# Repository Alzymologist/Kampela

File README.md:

# Kampela
Hardware signer and key storage for Substrate ecosystem.
https://kampe.la

-------------------------------------------------
As of September 2023, this monorepo became really hard to work with, and had been splitted into multiple ones under the new [Kalapaja](https://github.com/Kalapaja) organisation.  
⚠️ This repo is kept up for archival reasons, please submit any issues and pull requests in that new org instead.

The new repository structure under Kalapaja is the following:

| New repository | Original subfolder | Description |
|----------------|--------------------|-------------|
|[kampela-firmware](https://github.com/Kalapaja/kampela-firmware)|[`firmware/development`](https://github.com/Alzymologist/Kampela/tree/main/firmware/development)|Firmware sources and associated software projects|
|[kampela-hardware](https://github.com/Kalapaja/kampela-hardware)|['hardware/development'](https://github.com/Alzymologist/Kampela/tree/main/hardware/development)|Hardware design schematics and supplementary files|
|[kampela-common](https://github.com/Kalapaja/kampela-common)|['common'](https://github.com/Alzymologist/Kampela/tree/main/common)|Collection of shared libraries used by both "hot" and "cold" side of the project|
|[siltti](https://github.com/Kalapaja/siltti)|[application](https://github.com/Alzymologist/Kampela/tree/main/application)|Android companion app to interface with the device|
|[docs](https://github.com/Kalapaja/docs)|[docs/development](https://github.com/Alzymologist/Kampela/tree/main/docs/development)|Miscellaneous docs documenting different aspects of the project|

-------------------------------------------------

## Project summary
Kampela is a hardware version of Parity Signer. It is a small card-shaped device (ideally comparable to a credit card form factor, to be carried in a wallet when needed) that accepts data through unidirectional NFC port and shows output on a monochrome electronic paper screen. It has cryptographic strongbox with elliptic curves supported by Substrate —  which only stores private keys (after initial import) and performs all signing operations on-chip.

Kampela is designed to be a comparatively low-cost (below €100, in contrast to €500+ for a Signer-compatible smartphone) single-purpose device, which would only support a single seed phrase per unit, operated via a drastically simplified user interface. However, it would have all the security features of Parity Signer: a full-featured SURI account derivation system, transactions preview, metadata updates, logging.

As something that supports the same QR code output formats as Signer, it would be able to drop-in replace Signer when providing signatures back to a mobile/desktop wallet. The only challenge would be in transforming the current QR-driven input format of Signer into a suitable NFC payload. Alongside with native support in some apps (which would require software modification) this can also be achieved with a tiny “translator” app for a regular (online, not necessary trusted — one’s usual daily driver) mobile phone: it would snap a QR code with the transaction details and (statelessly, without any extra features or complicated UI) transform that into an NFC payload.

Kampela is a natural (and long-discussed) extension of Parity Signer to leverage the most out of modern hardware-based crypto chips and drastically reduce Signer’s attack surface: no mobile OS, not extra platform features, no unexpected communication methods or airplane mode to take care of.

Kampela is not a wallet! It is a signing tool, it is not able to track on-chain balances, validate things over chain-provided information or generate transactions on itself.

## Problem statement

Parity Signer project is a unique solution to provide user-friendly secure airgapped signing with seamless integration into ecosystem. However, there are certain problems that could not be solved at the moment:

Hardware cryptographic chips in modern phones do not support elliptic curve algorithms used in Substrate networks — so in result secrets being exposed to the main RAM of the device for the duration of usage (only hardware-encrypted at rest), where it may potentially leak or be accessed by malicious software.

Current hardware compatibility is limited: only newer iOS devices and few latest models of Android devices support hardware encryption of secrets. This puts supported devices on the more expensive side of the price range.

With iPod Touch being decommissioned, all devices currently in production which support necessary hardware features also include baseband chip — which runs a separate closed-source OS running on a separate, special-purpose chip while commonly having a full DMA access to the main phone’s memory. This chip could not be trusted (see Samsung’s baseband backdoor as an example) and has potential to leak secrets through radio channel or by use of kleptography, overriding on-board entropy generation or execution environment.

## Details

Kampela is an approximately credit card sized box with a rectangular screen and minimalistic controls (capacitive buttons alongside the screen or something similar — to be designed). In addition to development of the device itself (which will be available under suitable FOSS licenses both in terms of software and hardware designs), a reference MVP implementation of QR-to-NFC converter app will also be created.

After seed phrase initialization (either input or random generation — the latter being a potential technical challenge due to its computational/UX intensity and lack of entropy available) it will be stored in an hardware-backed encrypted storage. Address derivations could be created in Kampela either by passing derivation strings from mobile device via NFC (since those are not secret on their own) or by typing on the device itself (with some form of dictionary-driven assisted input, due to limited controls available); resulting public keys could be exported through QR codes, in the exactly the same way as with Parity Signer. Transactions for signing are sent into Kampela via NFC, their contents rendered on low-power e-ink monochrome screen and then user can unlock the device and sign transaction. Unidirectional nature and limited range/direction of both communication interfaces ensures that user remains in full control of data. Kampela has no battery (at least no battery for long-term power supply) and is powered only through NFC — which adds another layer of security, since no long-term backdoors can survive in RAM, and compromising the stored firmware itself is a much higher bar to clear for the attackers. Kampela will use a Secure Element or similar technology (like Arm TrustZone) to store secrets in a way, which will make it as hard as realistically possible to extract the secret keys, even with full physical access to the device and lab equipment being available.

Kampela is envisioned to be as close to open hardware criteria as possible, as long as it won’t compromise the resulting security model directly (for example, if requirement to support arbitrary user-provided firmware would clash with chosen security model, we would choose security model; all such cases would be clearly argumented and documented, of course). All security-sensitive parts of the device (NFC, RNG) would be implemented as much as possible through discrete, fixed-logic components (potentially with FPGA for the more uncommon parts of it, like sr25519  crypto) instead of being done “in software” or trusted to all-in-one integrated chip developers. Firmware for the programmable part of the device is to be written in Rust. On the smartphone companion app, it would use the same proven combination of Rust and native platform-dependent frameworks as Parity Signer currently does.

Unlike other projects in the similar problem space (which routinely withheld certain design specifications, and make others only available under an NDA, see, for example, discontinued project Cobo), we aim to make an extreme push to transparency of our designs, both on hardware and software layers. While this is expected to provide a boost in security and verifiability of Kampela devices, this severely restricts any potential future commercialization effort, since the competition (which wouldn't have to recover R&D costs) would undercut any official manufacturers on profit margins. We'd prefer this extreme competition to be a feature, not a bug; the only project with comparable manufacturing model would be Trezor, but it has a series of well-known shortcomings both in design and hardware choice areas.

## Ecosystem Fit

Currently, there are not too many options to securely handle keys in the Polkadot/Kusama ecosystem. There’s some Ledger support (which is often lagging behind the runtimes update cadence, and doesn’t exist for all the parachains out of the box), and Parity Signer and it’s fork Stylo (which requires an expensive smartphone device being used for this airgapped purpose only, and also has a much wider attack surface due to the device having a general-purpose OS and at least potential WiFi/3G/Bluetooth connectivity). We expect Kampela (having its own set of quite distinct tradeoffs) to supplement those two solutions — and integrate nicely with other layers of the tech stack (wallets, browser extensions etc), being a drop-in replacement of the currently already broadely supported Parity Signer.

## Origins of the name

Kampela, a flatfish — since the device is flat and is intended to resist phishing.

## Why Polkadot network?

Kampela project is a long-missing component to ultimately harden security of the whole Substrate ecosystem and ensure it’s secure and unstoppable status in long-term. Polkadot part of the greater ecosystem, as flagship and stable reference core, is natural space to develop universal solid solution like Kampela.

## Reviewers responses

Q: ​I think the NFC part isn’t very great from a usability perspective.

A: On contrary, NFC transfer of data into the device would be much smoother than with QR movies, especially for large payloads like metadata. The idea is that user will attach Kampela to the back of the smartphone, perform all the operations that do not require security with convenience of familiar smartphone interfaces, then flip the stack over and perform secure operations until output QR is shown. With QR presented on e-ink screen, Kampela could safely be detached from the phone as the QR intended for public broadcast would remain on screen. The task of mechanical engineer in this project (in addition to making device casing cheap to produce and robust) would be to ensure this flow is as comfortable and universal across the phones as possible.

Q: I guess the user does not really care about the RAM exposure as long as my phone is offline all the time.

A: Unfortunately, this is not so. The applications that could corrupt memory used by the signing application could manipulate RNG into leaking arbitrary data (including leaked secrets) through kleptography methods without exposing the leakage in any way. The leaked secrets could be broadcasted secretly through signature screen or other non-disabled communication methods via steganography. Finally, secrets leaked to memory could be stored outside of hardware encrypted storage negating its benefits in case attacker has physical access to the device reducing his need for fully-equipped forensic lab to relatively cheap and widespread memory dumping equipment. The Kampela solves these issues by lack of shared execution environment (and potentially rogue independent blackbox systems on board) and solid rust code with proper zeroization implemented.

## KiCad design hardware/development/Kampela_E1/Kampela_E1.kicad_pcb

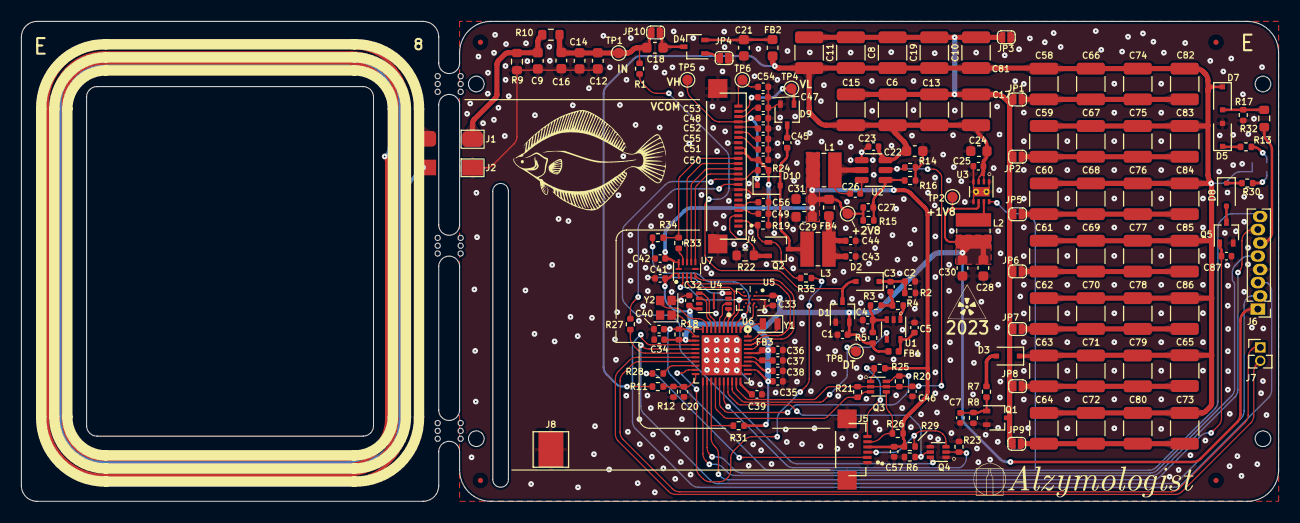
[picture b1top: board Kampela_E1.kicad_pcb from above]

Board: 2 copper layers, 120.5 x 46.0 mm, 188 parts (1 on the bottom side), 95 nets.

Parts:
C1, C4, C5, C20, C23, C25, C26, C32, C33, C35, C36, C37, C38, C40, C41, C42, C46: 0.1u; C_0402_1005Metric
C2: 82p; C_0402_1005Metric
C3, C27: 100p; C_0402_1005Metric
C6, C8, C10, C11, C13, C15, C17, C19, C58, C59, C60, C61, C62, C63, C64, C65, C66, C67, C68, C69, C70, C71, C72, C73, C74, C75, C76, C77, C78, C79, C80, C81, C82, C83, C84, C85, C86: 47x16; C_1210_3225Metric
C7: 1uF; C_0402_1005Metric
C9: NC; C_0603_1608Metric
C12, C14: 47; C_0603_1608Metric
C16: 100; C_0603_1608Metric
C18: 68; C_0603_1608Metric
C21, C22, C24: 10x16; C_0603_1608Metric
C28, C29, C30, C31: 22x6.3; C_0603_1608Metric
C34, C43, C45, C49, C52, C53, C56, C57, C87: 4.7x25; C_0402_1005Metric
C39, C47, C48, C50, C51, C54, C55: 1x50; C_0402_1005Metric
C44: 0.1; C_0402_1005Metric
D1: BAV99W; SOT-323_SC-70
D2, D7, D10: BAT54WS; D_SOD-323F
D3: BZX84J-B9V1; D_SOD-323F
D4, D9: BAS70-04W; SOT-323_SC-70
D5: D3Z13BF-7; D_SOD-323F
D8: D3Z5V1BF-7; D_SOD-323F
D12: SB0603WC01-RG; LED_DUAL_0603
FB1, FB3: BLM15AG102SZ1D; L_0402_1005Metric
FB2, FB4: BLM18KG102SN1D; L_0603_1608Metric
FID1, FID2, FID3, FID4: Fiducial; Fiducial_0.5mm_Mask1.5mm
H1, H2, H3, H4: MountingHole; MountingHole_2.1mm
J1, J2, J8: E_ANT; TestPoint_Pad_2.4x3.5mm
J4: E2154CS0C1; GDEY027T91-T01_bended
J5: TOUCH; HRS_FH34SRJ-6S-0.5SH(50)
J6: Conn_01x08; PinHeader_1x08_P1.27mm_Vertical_Prog
J7: Conn_01x02; PinHeader_1x02_P1.27mm_Vertical
JP1, JP2, JP3, JP4, JP5, JP6, JP7, JP8, JP9, JP10: SolderJumper_2_Open; SolderJumper_0.8.x1mm
L1: 3.3uH; L_Wuerth_MAPI-3015
L2: 2.2uH; L_Wuerth_MAPI-3015
L3: NR3015T100M; L_Wuerth_MAPI-3015
Q1, Q2: PMF250XNEX; SOT-323_SC-70
Q3, Q4: SSM6N35AFE; SOT-563
Q5: NX138BKWX; SOT-323_SC-70
R1: 6.8K; R_0402_1005Metric
R2: 53.6K; R_0402_1005Metric
R3: 22K; R_0402_1005Metric
R4: 47K; R_0402_1005Metric
R5: 100K; R_0402_1005Metric
R6, R7, R17, R18, R23, R24, R25, R26, R27, R28, R29: 10K; R_0402_1005Metric
R8, R11: 976K; R_0402_1005Metric
R9: 1K; R_0603_1608Metric
R10, R32: 2.2; R_0603_1608Metric
R12, R14: 150K; R_0402_1005Metric
R13: 10; R_0402_1005Metric
R15: 130K; R_0402_1005Metric
R16: 52.3K; R_0402_1005Metric
R19, R31: 470K; R_0402_1005Metric
R20, R21, R34, R35: 1K; R_0402_1005Metric
R22: 0.47R; R_0603_1608Metric
R30, R33: 100; R_0402_1005Metric
TP1, TP2, TP3, TP4, TP5, TP6, TP8: TestPoint; TestPoint_Pad_D1.0mm
U1: LMV7271; SOT-353_SC-70-5
U2: AP63200WU; TSOT-23-6
U3: TPS62171DSG; WSON-8-1EP_2x2mm_P0.5mm_EP0.9x1.6mm_ThermalVias
U4: APS6404L-SQN; SON-8-1EP_3x2mm_P0.5mm_EP1.4x1.6mm
U5: AT25XE321D-UUN-T; WLCSP 12-ball 3 x 2 x 3 Array
U6: EFM32PG23B200F512IM40; QFN-40_EP_5x5_Pitch0.4mm
U7: TXU0104PW; Texas_R-PUQFN-N12
Y1: FC2012AN; Crystal_SMD_2012-2Pin_2.0x1.2mm
Y2: 39MHz; Crystal_SMD_2016-4Pin_2.0x1.6mm
mouse-bite-2mm-slot, mouse-bite-2mm-slot#2, mouse-bite-2mm-slot#3: VAL**; mouse-bite-2mm_DEEP

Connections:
+1V8: C1.2, C28.2, C30.2, C32.1, C33.1, C34.2, C35.1, C36.1, C38.1, C41.2, D1.2 (K), FB1.1, FB3.2, J6.1, L2.2, R5.1, R18.2, R31.1, TP2.1, U3.6 (VOS), U4.8 (VCC), U5.B2 (VCC), U6.12 (DVDD), U6.32 (VREGVDD), U6.34 (DVDD), U6.36 (IOVDD), U7.1 (VCCA)
+2V8: C27.1, C29.2, C31.2, C42.1, C50.2, C57.1, FB4.2, J4.15, J4.16, J5.4, L1.2, R15.1, R24.2, R25.1, R26.1, R29.2, TP3.1, U7.11 (VCCB), U7.12 (OE)
/Display/2V8_EN: C46.1, Q3.2 (G), Q3.5 (G), R14.2, R20.2, R21.2, U2.2 (EN), U6.29 (PA09)
/Display/BUSY: R27.2, U6.15 (PB04)
/Display/E_BUSY: J4.9, R27.1
/Display/E_CS: U6.38 (PD02), U7.4 (A3)
/Display/E_D/C: U6.37 (PD03), U7.5 (A4)
/Display/E_MISO: R34.1, U5.D4 (IO1/SO), U6.2 (PC01)
/Display/E_RES: J4.10, Q4.6 (D), R24.1
/Display/E_SCK: U5.F2 (SCK), U6.4 (PC03), U7.3 (A2)
/Display/E_SDI: U5.E3 (SI/IO0), U6.3 (PC02), U7.2 (A1)
/Display/GDR: J4.2, Q2.1 (G), R19.1, R35.1
/Display/H_CS: J4.12, U7.8 (B3)
/Display/H_D/C: J4.11, U7.7 (B4)
/Display/H_SCK: J4.13, U7.9 (B2)
/Display/H_SDI: J4.14, R33.1, R34.2
/Display/INT: R28.2, U6.18 (PB01)
/Display/POW: C43.2, C44.1, FB4.1, L3.1
/Display/PREVGH: C48.1, D10.1 (K), J4.21, TP5.1
/Display/PREVGL: C47.1, D9.1, J4.23, TP4.1
/Display/RES: Q4.2 (G), R23.2, U6.26 (PA06)
/Display/RESE: J4.3, Q2.2 (S), R22.1
/Display/RES_TC: Q4.5 (G), R6.2, U6.27 (PA07)
/Display/SCL: Q3.3 (D), R21.1, U6.24 (PA04)
/Display/SDA: Q3.6 (D), R20.1, U6.25 (PA05)
/Display/T_INT: J5.2, R28.1
/Display/T_RES: J5.3, Q4.3 (D), R29.1
/Display/T_SCL: J5.5, Q3.4 (S), R26.2
/Display/T_SDA: J5.6, Q3.1 (S), R25.2
/Display/VCOM: C54.2, J4.24, TP6.1
/MCU/DATA: TP8.1, U1.4, U6.28 (PA08)
/MCU/FLASH_CS: U5.B4 (~CS), U6.1 (PC00)
/MCU/HV: C6.2, C8.2, C10.2, C11.2, C13.2, C15.2, C17.2, C19.2, C22.2, C23.1, C24.2, C25.1, C58.2, C59.2, C60.2, C61.2, C62.2, C63.2, C64.2, C65.2, C66.2, C67.2, C68.2, C69.2, C70.2, C71.2, C72.2, C73.2, C74.2, C75.2, C76.2, C77.2, C78.2, C79.2, C80.2, C81.2, C82.2, C83.2, C84.2, C85.2, C86.2, D3.1 (K), D7.1 (K), D12.2 (K1), D12.4 (K2), FB2.1, R11.1, U2.3 (IN), U3.2 (VIN), U3.3 (EN)
/MCU/P_GOOD: C40.1, J6.8, R18.1, U3.8 (PG), U6.11 (~RESET)
/MCU/P_IN: J6.6, R32.1
/MCU/RAM_CS: U4.1 (~CE), U6.5 (PC04)
/MCU/RX: J6.2, U6.14 (PB05)
/MCU/R_MISO: U4.2 (SO/SIO), U6.6 (PC05)
/MCU/R_MOSI: U4.5 (SI/SIO), U6.7 (PC06)
/MCU/R_SCK: U4.6 (SCLK), U6.8 (PC07)
/MCU/SWDCK: J6.7, U6.21 (PA01)
/MCU/SWDIO: J6.5, U6.22 (PA02)
/MCU/TX: J6.3, U6.13 (PB06)
/MCU/V_CHK: C20.1, R11.2, R12.1, U6.20 (PA00)
/MCU/~MCU_OK: C87.2, Q5.1 (G), R31.2, U6.23 (PA03)
/Power/CN: C6.1, C8.1, C10.1, C11.1, C13.1, C15.1, C17.1, C19.1, C81.1, JP1.1 (A), JP2.2 (B), JP3.2 (B), JP5.1 (A), JP6.2 (B), JP7.1 (A), JP8.2 (B), JP9.1 (A), Q1.3 (D)
/Power/IN_DT: C12.1, C14.1, C16.1, C18.1, JP10.2 (B), R1.1, R10.2, TP1.1
GND: C1.1, C2.2, C4.1, C5.1, C7.2, C9.2, C12.2, C14.2, C16.2, C20.2, C21.1, C22.1, C23.2, C24.1, C25.2, C28.1, C29.1, C30.1, C31.1, C32.2, C33.2, C34.1, C35.2, C36.2, C37.2, C38.2, C39.1, C40.2, C41.1, C42.2, C43.1, C44.2, C46.2, C47.2, C48.2, C49.1, C50.1, C51.1, C52.1, C53.1, C54.1, C55.1, C56.1, C57.2, C87.1, D1.1 (A), D5.2 (A), D9.2, J2.1, J4.8, J4.17, J4.S2 (S), J5.1, J5.S2 (S), J6.4, J8.1, JP3.1 (A), JP4.1 (A), Q1.2 (S), Q4.1 (S), Q4.4 (S), Q5.2 (S), R2.2, R6.1, R8.2, R9.1, R12.2, R14.1, R16.2, R17.2, R19.2, R22.2, R23.1, U1.2 (V-), U2.4 (GND), U3.1 (PGND), U3.4 (AGND), U3.5 (FB), U3.9 (PAD), U4.4 (VSS), U5.C3 (GND), U6.33 (VREGVSS), U6.41 (VSS), U7.6 (GND), Y2.2
unnamed: C3.1, R3.1, R4.2
unnamed: C21.2, D4.2, FB2.2
unnamed: C45.1, D9.3
unnamed: D1.3 (common), D2.2 (A), R1.2
unnamed: C2.1, C3.2, D2.1 (K), R2.1
unnamed: D3.2 (A), R7.1
unnamed: D5.1 (K), R13.2
unnamed: D7.2 (A), R17.1, R32.2
unnamed: D8.2 (A), Q5.3 (D)
unnamed: D8.1 (K), R30.2
unnamed: C45.2, D10.2 (A), L3.2, Q2.3 (D)
unnamed: D12.1 (A1), R13.1
unnamed: D12.3 (A2), R30.1
unnamed: C9.1, J1.1, R9.2, R10.1
unnamed: C49.2, J4.4
unnamed: C56.2, J4.5
unnamed: C51.2, J4.18
unnamed: C55.2, J4.19
unnamed: C52.2, J4.20
unnamed: C53.2, J4.22
unnamed: J7.1, U6.17 (PB02)
unnamed: J7.2, U6.16 (PB03)
unnamed: C58.1, C66.1, C74.1, C82.1, JP1.2 (B)
unnamed: C59.1, C67.1, C75.1, C83.1, JP2.1 (A)
unnamed: D4.1, JP4.2 (B)
unnamed: C60.1, C68.1, C76.1, C84.1, JP5.2 (B)
unnamed: C61.1, C69.1, C77.1, C85.1, JP6.1 (A)
unnamed: C62.1, C70.1, C78.1, C86.1, JP7.2 (B)
unnamed: C63.1, C65.1, C71.1, C79.1, JP8.1 (A)
unnamed: C64.1, C72.1, C73.1, C80.1, JP9.2 (B)
unnamed: C18.2, D4.3, JP10.1 (A)
unnamed: C7.1, Q1.1 (G), R7.2, R8.1
unnamed: R4.1, U1.1 (+)
unnamed: C4.2, R3.2, R5.2, U1.3 (-)
unnamed: C5.2, FB1.2, U1.5 (V+)
unnamed: C26.2, U2.6 (BST)
unnamed: C27.2, R15.2, R16.1, U2.1 (FB)
unnamed: C26.1, L1.1, U2.5 (SW)
unnamed: L2.1, U3.7 (SW)
unnamed: C37.1, FB3.1, U6.35 (AVDD)
unnamed: C39.2, U6.30 (CAP)
unnamed: U6.9 (HFXTAL_I), Y2.3
unnamed: U6.10 (HFXTAL_O), Y2.1
unnamed: R35.2, U6.19 (PB00)
unnamed: U6.40 (PD00), Y1.2
unnamed: U6.39 (PD01), Y1.1
unnamed: R33.2, U7.10 (B1)

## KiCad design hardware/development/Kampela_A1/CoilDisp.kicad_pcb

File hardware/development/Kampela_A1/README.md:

# CoilDisp

This devboard uses `STN32L432KCU` mc to test power harvesting to power a e-ink screen.

## Power harvest

The board supports connection of printed coil or external coil. Additionally, a UFL connector for VNA for coil model parameters analysis is implemented

## Power storage

The power is stored in smd ceramic capacitors; external connections for electrolytic capacitors to support londer unpowered states and balance high poewr consumption during screen refresh cycle are implemented

## Screen

The component for testing is PervasiveDisplays model E2154CS0C1

[Datasheet](https://www.pervasivedisplays.com/wp-content/uploads/2021/12/1P255-00_03_E2154CS0C1_202111203doc.pdf) and [programming guide](https://docs.pervasivedisplays.com/epd-usage/epd-driving-sequence/small-epds) are available at PervasiveDisplays website.

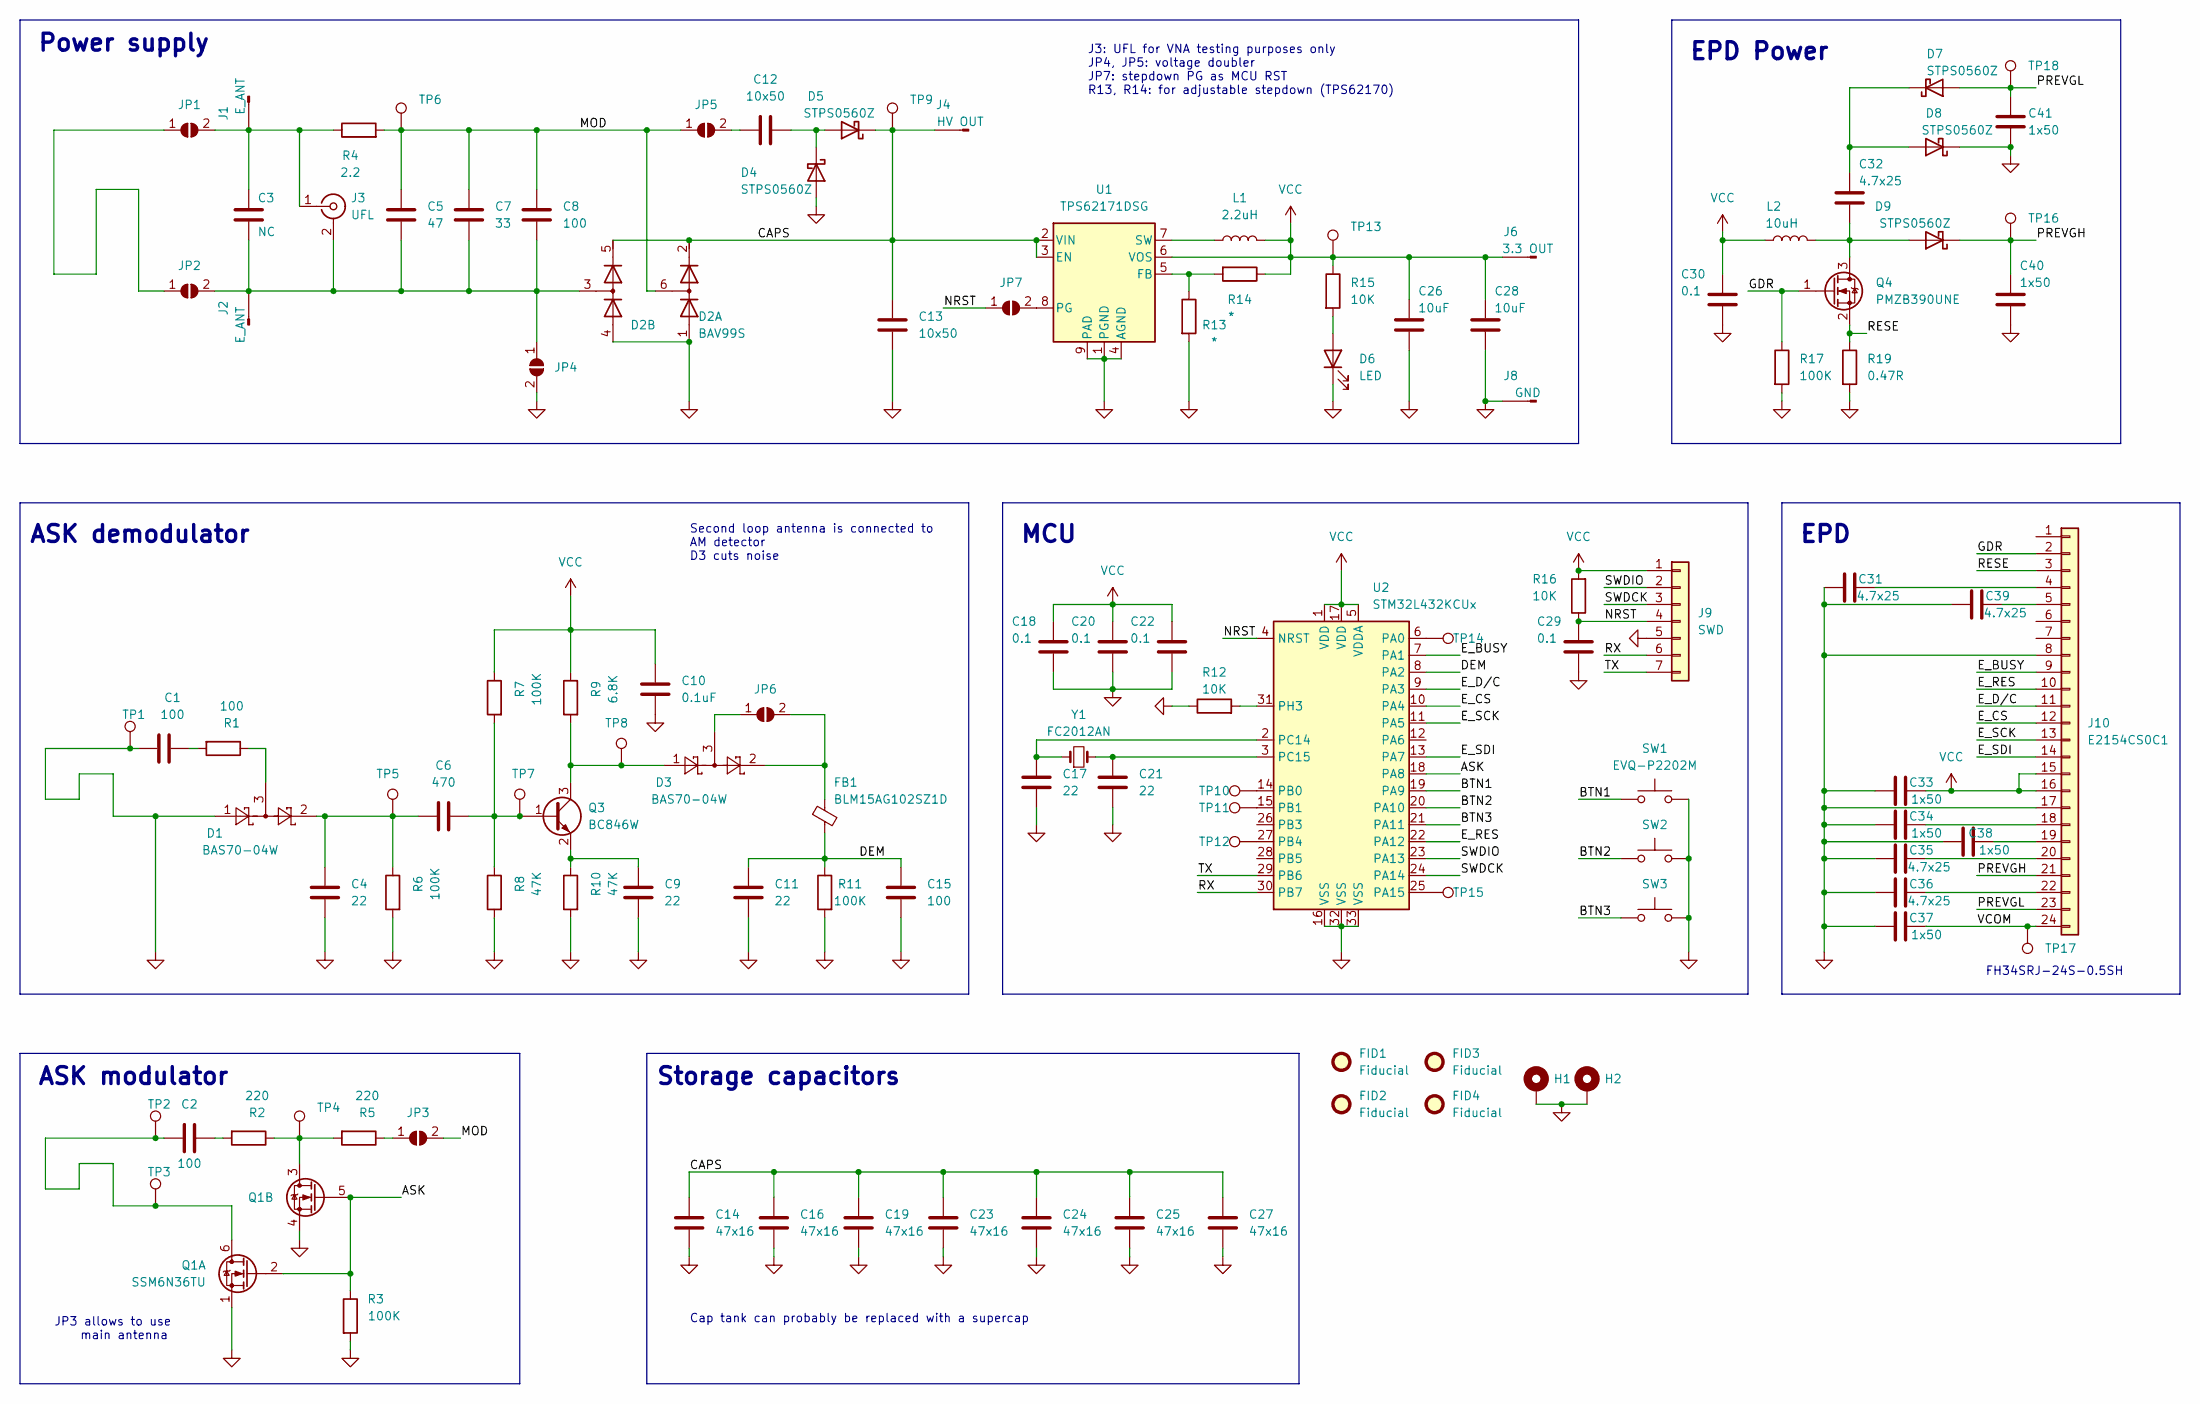
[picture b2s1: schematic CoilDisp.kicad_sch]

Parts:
C1, C2, C8: 100; C_0603_1608Metric
C3: NC; C_0603_1608Metric
C4, C9, C11, C17, C21: 22; C_0402_1005Metric
C5: 47; C_0603_1608Metric
C6: 470; C_0402_1005Metric
C7: 33; C_0603_1608Metric
C10: 0.1uF; C_0402_1005Metric
C12: 10x50; C_0603_1608Metric
C13: 10x50; C_1206_3216Metric
C14, C16, C19, C23, C24, C25, C27: 47x16; C_1210_3225Metric
C15: 100; C_0402_1005Metric
C18, C20, C22, C29, C30: 0.1; C_0402_1005Metric
C26, C28: 10uF; C_0603_1608Metric
C31, C32, C35, C36, C39: 4.7x25; C_0402_1005Metric
C33, C34, C37, C38, C40, C41: 1x50; C_0402_1005Metric
D1, D3: BAS70-04W; SOT-323_SC-70
D2: BAV99S; SOT-563
D4, D5, D7, D8, D9: STPS0560Z; D_SOD-123F
D6: LED; LED_0603_1608Metric
FB1: BLM15AG102SZ1D; L_0402_1005Metric
FID1, FID2, FID3, FID4: Fiducial; Fiducial_0.5mm_Mask1.5mm
H1, H2: MountingHole_Pad; MountingHole_3.2mm_M3_DIN965_Pad_TopBottom
J1, J2: E_ANT; TestPoint_THTPad_D1.0mm_Drill0.5mm
J3: UFL; U.FL_Hirose_U.FL-R-SMT-1_Vertical
J4: HV OUT; TestPoint_THTPad_D1.0mm_Drill0.5mm
J6: 3.3 OUT; TestPoint_THTPad_D1.0mm_Drill0.5mm
J8: GND; TestPoint_THTPad_D1.0mm_Drill0.5mm
J9: SWD; PinHeader_1x07_P2.54mm_Vertical
J10: E2154CS0C1; HRS_FH34SRJ-24S-0.5SH(99)
JP1, JP2, JP3, JP4, JP5, JP6, JP7: SolderJumper_2_Open; SolderJumper-2_P1.3mm_Open_RoundedPad1.0x1.5mm
L1: 2.2uH; L_Wuerth_MAPI-3015
L2: 10uH; L_Vishay_IHLP-2020
Q1: SSM6N36TU; SOT-363_SC-70-6
Q3: BC846W; SOT-323_SC-70
Q4: PMZB390UNE; Diodes_DFN1006-3
R1: 100; R_0402_1005Metric
R2, R5: 220; R_0603_1608Metric
R3, R6, R7, R11, R17: 100K; R_0402_1005Metric
R4: 2.2; R_0603_1608Metric
R8, R10: 47K; R_0402_1005Metric
R9: 6.8K; R_0402_1005Metric
R12, R15, R16: 10K; R_0402_1005Metric
R13, R14: *; R_0603_1608Metric
R19: 0.47R; R_0603_1608Metric
SW1, SW2, SW3: EVQ-P2202M
TP1, TP2, TP3, TP4, TP5, TP6, TP7, TP8, TP9, TP10, TP11, TP12, TP13, TP14, TP15, TP16, TP17, TP18: TestPoint; TestPoint_Pad_D1.0mm
U1: TPS62171DSG; WSON-8-1EP_2x2mm_P0.5mm_EP0.9x1.6mm_ThermalVias
U2: STM32L432KCUx; QFN-32-1EP_5x5mm_P0.5mm_EP3.45x3.45mm
Y1: FC2012AN; Crystal_SMD_2012-2Pin_2.0x1.2mm

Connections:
/ASK: Q1.2 (G), Q1.5 (G), R3.1, U2.18 (PA8)
/BTN1: SW1.1, U2.19 (PA9)
/BTN2: SW2.1, U2.20 (PA10)
/BTN3: SW3.1, U2.21 (PA11)
/CAPS: C13.2, C14.2, C16.2, C19.2, C23.2, C24.2, C25.2, C27.2, D2.2 (K2), D2.5 (K4), D5.1 (K), J4.1, TP9.1, U1.2 (VIN), U1.3 (EN)
/DEM: C11.2, C15.2, FB1.2, R11.1, U2.8 (PA2)
/E_BUSY: J10.9, U2.7 (PA1)
/E_CS: J10.12, U2.10 (PA4)
/E_D/C: J10.11, U2.9 (PA3)
/E_RES: J10.10, U2.22 (PA12)
/E_SCK: J10.13, U2.11 (PA5)
/E_SDI: J10.14, U2.13 (PA7)
/GDR: J10.2, Q4.1 (G), R17.1
/MOD: C5.1, C7.1, C8.1, D2.6 (K3A4), JP3.2 (B), JP5.1 (A), R4.2, TP6.1; also elsewhere on the board
/NRST: C29.1, J9.4, JP7.1 (A), R16.1, U2.4 (NRST)
/PREVGH: C40.1, D9.1 (K), J10.21, TP16.1; also elsewhere on the board
/PREVGL: C41.1, D7.2 (A), J10.23, TP18.1; also elsewhere on the board
/RESE: J10.3, Q4.2 (S), R19.1
/RX: J9.6, U2.30 (PB7)
/SWDCK: J9.3, U2.24 (PA14)
/SWDIO: J9.2, U2.23 (PA13)
/TX: J9.7, U2.29 (PB6)
/VCOM: C37.2, J10.24, TP17.1; also elsewhere on the board
GND: C1.1, C4.2, C9.1, C10.1, C11.1, C13.1, C14.1, C15.1, C16.1, C17.1, C18.2, C19.1, C20.2, C21.1, C22.2, C23.1, C24.1, C25.1, C26.2, C27.1, C28.2, C29.2, C30.2, C31.1, C33.1, C34.1, C35.1, C36.1, C37.1, C38.1, C39.1, C40.2, C41.2, D1.1, D2.1 (A1), D2.4 (A3), D4.2 (A), D6.1 (K), D8.1 (K), H1.1, H2.1, J8.1, J9.5, J10.8, J10.17, JP4.2 (B), Q1.1 (S), Q1.4 (S), R3.2, R6.2, R8.2, R10.2, R11.2, R12.1, R13.2, R17.2, R19.2, SW1.2, SW2.2, SW3.2, TP1.1, U1.1 (PGND), U1.4 (AGND), U1.9 (PAD), U2.16 (VSS), U2.32 (VSS), U2.33 (VSS)
unnamed: C1.2, R1.2
unnamed: C2.1, Q1.6 (D), TP2.1, TP3.1
unnamed: C2.2, R2.2
unnamed: C3.1, J1.1, J3.1 (In), JP1.2 (B), R4.1
unnamed: C3.2, C5.2, C7.2, C8.2, D2.3 (K1A2), J2.1, J3.2 (Ext), JP2.2 (B), JP4.1 (A)
unnamed: C4.1, C6.1, D1.2, R6.1, TP5.1
unnamed: C6.2, Q3.1 (B), R7.2, R8.1, TP7.1
unnamed: C9.2, Q3.2 (E), R10.1
unnamed: C12.1, D4.1 (K), D5.2 (A)
unnamed: C12.2, JP5.2 (B)
unnamed: C17.2, U2.2 (PC14), Y1.1
unnamed: C21.2, U2.3 (PC15), Y1.2
unnamed: C31.2, J10.4
unnamed: C32.1, D7.1 (K), D8.2 (A)
unnamed: C32.2, D9.2 (A), L2.2, Q4.3 (D)
unnamed: C34.2, J10.18
unnamed: C35.2, J10.20
unnamed: C36.2, J10.22
unnamed: C38.2, J10.19
unnamed: C39.2, J10.5
unnamed: D1.3, R1.1
unnamed: D3.1, Q3.3 (C), R9.2, TP8.1
unnamed: D3.2, FB1.1, JP6.2 (B)
unnamed: D3.3, JP6.1 (A)
unnamed: D6.2 (A), R15.2
unnamed: JP1.1 (A), JP2.1 (A)
unnamed: JP3.1 (A), R5.1
unnamed: JP7.2 (B), U1.8 (PG)
unnamed: L1.1, U1.7 (SW)
unnamed: Q1.3 (D), R2.1, R5.2, TP4.1
unnamed: R12.2, U2.31 (PH3)
unnamed: R13.1, R14.2, U1.5 (FB)
unnamed 56: TP10.1, U2.14 (PB0); also elsewhere on the board
unnamed 57: TP11.1, U2.15 (PB1); also elsewhere on the board
unnamed 58: TP12.1, U2.27 (PB4); also elsewhere on the board
unnamed 59: TP14.1, U2.6 (PA0); also elsewhere on the board
unnamed 60: TP15.1, U2.25 (PA15); also elsewhere on the board
VCC: C10.2, C18.1, C20.1, C22.1, C26.1, C28.1, C30.1, C33.2, J6.1, J9.1, J10.15, J10.16, L1.2, L2.1, R7.1, R9.1, R14.1, R15.1, R16.2, TP13.1, U1.6 (VOS), U2.1 (VDD), U2.5 (VDDA), U2.17 (VDD)

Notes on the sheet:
ASK modulator
MCU
Power supply
EPD
Storage capacitors
FH34SRJ-24S-0.5SH
Second loop antenna is connected to AM detector D3 cuts noise
J3: UFL for VNA testing purposes only JP4, JP5: voltage doubler JP7: stepdown PG as MCU RST R13, R14: for adjustable stepdown (TPS62170)
ASK demodulator
Cap tank can probably be replaced with a supercap
JP3 allows to use main antenna
EPD Power

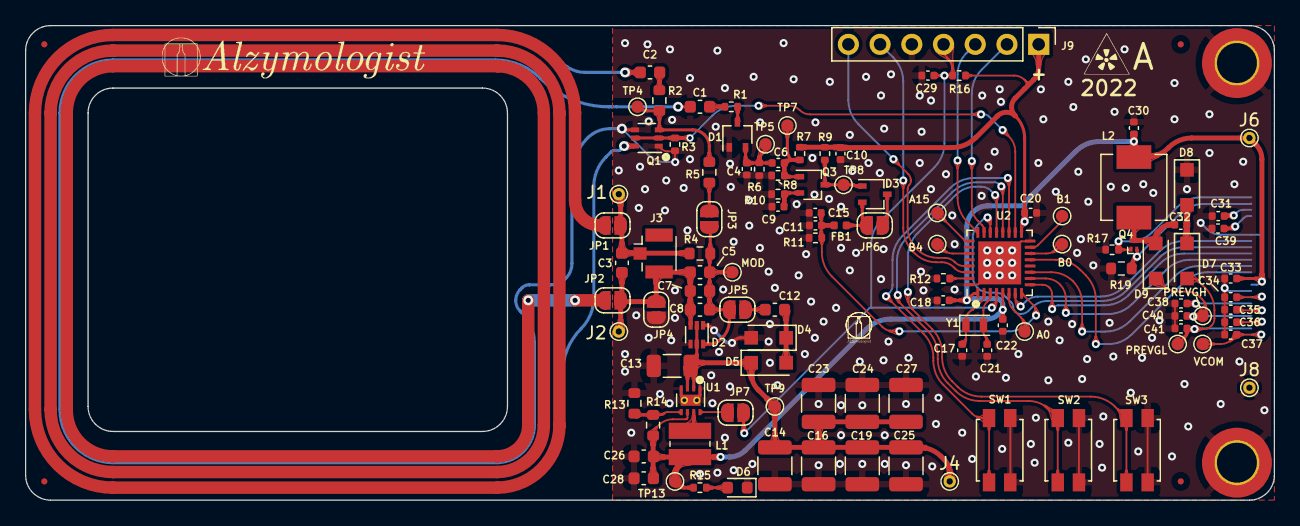
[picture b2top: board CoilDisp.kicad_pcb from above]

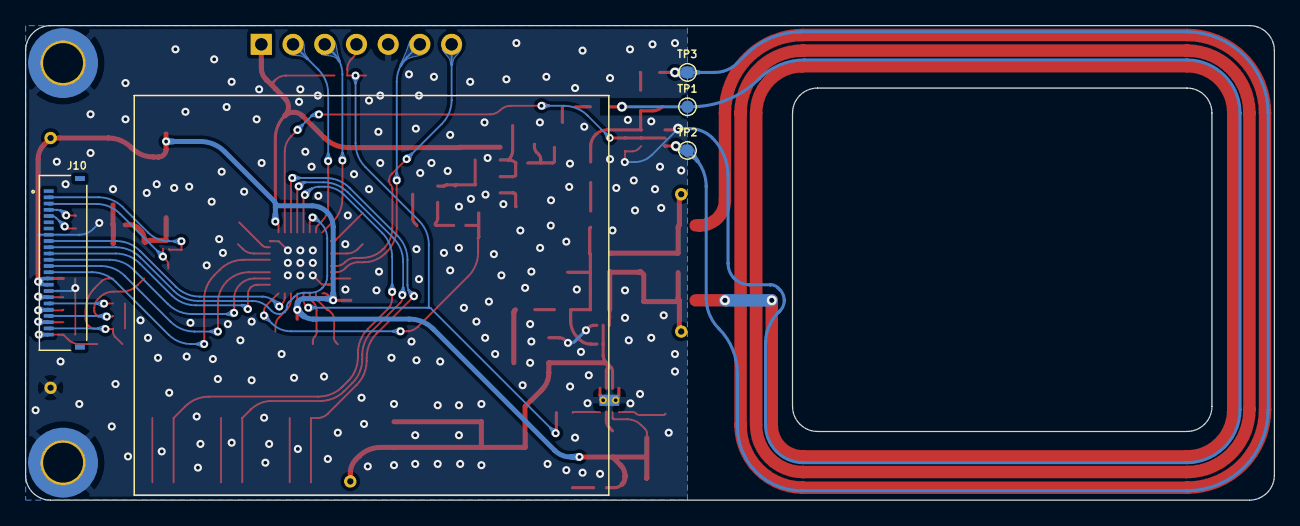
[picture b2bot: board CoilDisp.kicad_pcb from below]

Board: 2 copper layers, 100.0 x 38.0 mm, 119 parts (4 on the bottom side), 62 nets.

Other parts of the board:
A0, A15: TestPoint; TestPoint_Pad_D1.0mm
B0, B1, B4: TestPoint; TestPoint_Pad_D1.0mm
MOD: TestPoint; TestPoint_Pad_D1.0mm
PREVGH: TestPoint; TestPoint_Pad_D1.0mm
PREVGL: TestPoint; TestPoint_Pad_D1.0mm
VCOM: TestPoint; TestPoint_Pad_D1.0mm

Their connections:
/MOD: MOD.1; also elsewhere on the board
/PREVGH: PREVGH.1; also elsewhere on the board
/PREVGL: PREVGL.1; also elsewhere on the board
/VCOM: VCOM.1; also elsewhere on the board
unnamed 56: B0.1; also elsewhere on the board
unnamed 57: B1.1; also elsewhere on the board
unnamed 58: B4.1; also elsewhere on the board
unnamed 59: A0.1; also elsewhere on the board
unnamed 60: A15.1; also elsewhere on the board

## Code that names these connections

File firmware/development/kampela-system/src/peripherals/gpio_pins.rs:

//! Map GPIO pins

#![allow(dead_code)]

use cortex_m::asm::delay;
use efm32pg23_fix::GPIO_S;

// PA

pub const MCU_OK: u8 = 3;
pub const SCL_PIN: u8 = 4;
pub const SDA_PIN: u8 = 5;
pub const DISP_RES_PIN: u8 = 6;
pub const TOUCH_RES_PIN: u8 = 7;
pub const NFC_PIN: u8 = 8;
pub const POW_PIN: u8 = 9;

// PB

pub const TOUCH_INT_PIN: u8 = 1;
pub const SPI_BUSY_PIN: u8 = 4;

// PC
pub const FLASH_CS_PIN: u8 = 0;
pub const E_MISO_PIN: u8 = 1;
pub const E_MOSI_PIN: u8 = 2;
pub const E_SCK_PIN: u8 = 3;
pub const PSRAM_CS_PIN: u8 = 4;
pub const PSRAM_MISO_PIN: u8 = 5;
pub const PSRAM_MOSI_PIN: u8 = 6;
pub const PSRAM_SCK_PIN: u8 = 7;

// PD
pub const DISP_CS_PIN: u8 = 2;
pub const DISP_DC_PIN: u8 = 3;


/// Macro to switch a specific pin on a specific port.
///
/// At this point GPIO must be already clocked from elsewhere and port must be
/// in correct mode.
///
/// This does not change previously set bits.
macro_rules! gpio_pin {
    ($(#[$attr_set:meta] #[$attr_clear:meta] #[$attr_common:meta] $func_set: ident, $func_clear: ident, $port: tt, $pin: tt), *) => {
        $(
            #[$attr_set]
            #[$attr_common]
            pub fn $func_set(gpio: &mut GPIO_S) {
                gpio
                    .$port
                    .modify(|r, w| w.dout().variant(r.dout().bits() | (1 << $pin)));
            }

            #[$attr_clear]
            #[$attr_common]
            pub fn $func_clear(gpio: &mut GPIO_S) {
                gpio
                    .$port
                    .modify(|r, w| w.dout().variant(r.dout().bits() ^ (1 << $pin)));
            }
        )*
    }
}

// Prepare GPIO pins

gpio_pin!(
    /// Set MCU_OK status:
    /// Clear MCU_OK status:
    /// port A, pin [`MCU_OK`].
    mcu_ok_set,
    mcu_ok_clear,
    porta_dout,
    MCU_OK
);

gpio_pin!(
    /// Set flash chip select:
    /// Clear flash chip select:
    /// port C, pin [`FLASH_CS_PIN`].
    flash_chip_select_set,
    flash_chip_select_clear,
    portc_dout,
    FLASH_CS_PIN
);

gpio_pin!(
    /// Set display chip select:
    /// Clear display chip select:
    /// port D, pin [`DISP_CS_PIN`].
    display_chip_select_set,
    display_chip_select_clear,
    portd_dout,
    DISP_CS_PIN
);

gpio_pin!(
    /// Set display data/command:
    /// Clear display data/command:
    /// port D, pin [`DISP_DC_PIN`].
    display_data_command_set,
    display_data_command_clear,
    portd_dout,
    DISP_DC_PIN
);

gpio_pin!(
    /// Set display reset:
    /// Clear display reset:
    /// port A, pin [`DISP_RES_PIN`].
    display_res_set,
    display_res_clear,
    porta_dout,
    DISP_RES_PIN
);

gpio_pin!(
    /// Set touch reset:
    /// Clear touch reset:
    /// port A, pin [`TOUCH_RES_PIN`].
    touch_res_set,
    touch_res_clear,
    porta_dout,
    TOUCH_RES_PIN
);

gpio_pin!(
    /// scl set:
    /// scl clear:
    /// port A, pin [`SCL_PIN`].
    scl_set,
    scl_clear,
    porta_dout,
    SCL_PIN
);

gpio_pin!(
    /// sda set:
    /// sda clear:
    /// port A, pin [`SDA_PIN`].
    sda_set,
    sda_clear,
    porta_dout,
    SDA_PIN
);

gpio_pin!(
    /// Set power:
    /// Clear power:
    /// port A, pin [`POW_PIN`].
    pow_set,
    pow_clear,
    porta_dout,
    POW_PIN
);

gpio_pin!(
    /// Set MISO:
    /// Clear MISO:
    /// port A, pin [`E_MISO_PIN`].
    miso_set,
    miso_clear,
    portc_dout,
    E_MISO_PIN
);

gpio_pin!(
    /// Set MOSI:
    /// Clear MOSI:
    /// port A, pin [`E_MOSI_PIN`].
    mosi_set,
    mosi_clear,
    portc_dout,
    E_MOSI_PIN
);

gpio_pin!(
    /// Set SCK:
    /// Clear SCK:
    /// port A, pin [`E_SCK_PIN`].
    sck_set,
    sck_clear,
    portc_dout,
    E_SCK_PIN
);

gpio_pin!(
    /// Set PSRAM CS:
    /// Clear PSRAM CS:
    /// port C, pin [`PSRAM_CS_PIN`].
    psram_chip_select_set,
    psram_chip_select_clear,
    portc_dout,
    PSRAM_CS_PIN
);

gpio_pin!(
    /// Set PSRAM MISO:
    /// Clear PSRAM MISO:
    /// port C, pin [`PSRAM_MISO_PIN`].
    psram_miso_set,
    psram_miso_clear,
    portc_dout,
    PSRAM_MISO_PIN
);

gpio_pin!(
    /// Set PSRAM MOSI:
    /// Clear PSRAM MOSI:
    /// port C, pin [`PSRAM_MOSI_PIN`].
    psram_mosi_set,
    psram_mosi_clear,
    portc_dout,
    PSRAM_MOSI_PIN
);

gpio_pin!(
    /// Set PSRAM SCK:
    /// Clear PSRAM SCK:
    /// port C, pin [`PSRAM_SCK_PIN`].
    psram_sck_set,
    psram_sck_clear,
    portc_dout,
    PSRAM_SCK_PIN
);

gpio_pin!(
    /// Set NFC pin:
    /// Clear NFC pin:
    /// port A, pin [`NFC_PIN`].
    nfc_pin_set,
    nfc_pin_clear,
    porta_dout,
    NFC_PIN
);

/// GPIO initializations
pub fn init_gpio(gpio: &mut GPIO_S) {
    map_gpio(gpio);
    set_gpio_pins(gpio);
    set_external_interrupts(gpio);
}

/// Set GPIO functions
fn map_gpio(gpio: &mut GPIO_S) {
    gpio
        .porta_model
        .write(|w_reg| {
            w_reg
                .mode3().pushpull() // MCU operational indicator
                .mode4().wiredandpullup() // SCL for USART (display)
                .mode5().wiredandpullup() // SDA for USART (display)
                .mode6().pushpull() // Display reset
                .mode7().pushpull() // Touch reset
    });
    gpio
        .porta_modeh
        .write(|w_reg| {
            w_reg
                .mode0().inputpullfilter() // NFC
                .mode1().pushpull() // Power 2.8 V
    });
    gpio
        .portb_model
        .write(|w_reg| {
            w_reg
                .mode1().input() // interrupts from display sensor
                .mode4().input() // BUSY spi
    });
    gpio
        .portc_model
        .write(|w_reg| {
            w_reg
                .mode0().pushpull() // Flash chip select
                .mode1().inputpull() // Display MISO
                .mode2().pushpull() // Display MOSI
                .mode3().pushpull() //Display SCK
                .mode4().pushpull() // PSRAM chip select
                .mode5().inputpull() // PSRAM MISO
                .mode6().pushpull() // PSRAM MOSI
                .mode7().pushpull() // PSRAM SCK
    });
    gpio
        .portd_model
        .write(|w_reg| {
            w_reg
                .mode2().inputpull() // Display chip select
                .mode3().pushpull() // Display data/command
    });
}

/// Set GPIO pins to their starting values
fn set_gpio_pins(gpio: &mut GPIO_S) {
    mcu_ok_clear(gpio);
    mcu_ok_clear(gpio);
    pow_set(gpio);
    delay(100000); // wait after power set! (epaper manual for 2.8V setup)
    display_chip_select_set(gpio);
    display_data_command_clear(gpio);
    display_res_clear(gpio);
    sda_set(gpio);
    scl_set(gpio);
    flash_chip_select_set(gpio);
    miso_set(gpio);
    mosi_set(gpio);
    sck_clear(gpio);
    psram_chip_select_set(gpio);
    psram_miso_set(gpio);
    psram_mosi_clear(gpio);
    psram_sck_clear(gpio);
    nfc_pin_clear(gpio);
}

/// Set up external interrupt pins (used to get touch events from touch pad)
fn set_external_interrupts(gpio: &mut GPIO_S) {
    gpio
        .extipsell
        .write(|w_reg| w_reg.extipsel0().portb());
    gpio
        .extipinsell
        .write(|w_reg| w_reg.extipinsel0().pin1());
    gpio
        .extirise
        .write(|w_reg| w_reg.extirise().variant(0));
    gpio
        .extifall
        .write(|w_reg| w_reg.extifall().variant(1 << 0));
    gpio
        .ien
        .write(|w_reg| w_reg.extien0().set_bit());
}
